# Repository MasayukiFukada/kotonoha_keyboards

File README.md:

# ことのは キーボード(Kotonoha Keyboards)

My designed mechanical keyboards.

Firmware is [here](https://github.com/MasayukiFukada/qmk_firmware/tree/append_minamo_keymaps/keyboards/kotonoha) (QMK fork)  
※ `append_minamo_keymaps` branch

## ことのは 『盆栽』(Kotonoha - type "BONSAI")

* 30 % Keyboard (30 Key)
* FreeStyle Staggered
* PCB and Acrylic plate

## ことのは 『居合』(Kotonoha - type "IAI")

* 30 % Keyboard (30 Key)
* 6 x 2 OrtholinearBar
* PCB and Acrylic plate

## ことのは 『侘寂』(Kotonoha - type "WABISABI")

* 30 % Keyboard (30 Key)
* Matrix Staggered (Row x Column Staggered)
* PCB and Acrylic plate

## License

MIT

KiCad のフットプリントは [@foostan](https://github.com/foostan) さんのライブラリ  
[kbd](https://github.com/foostan/kbd) から使用させて頂きました。  
foostan さんありがとうございました。

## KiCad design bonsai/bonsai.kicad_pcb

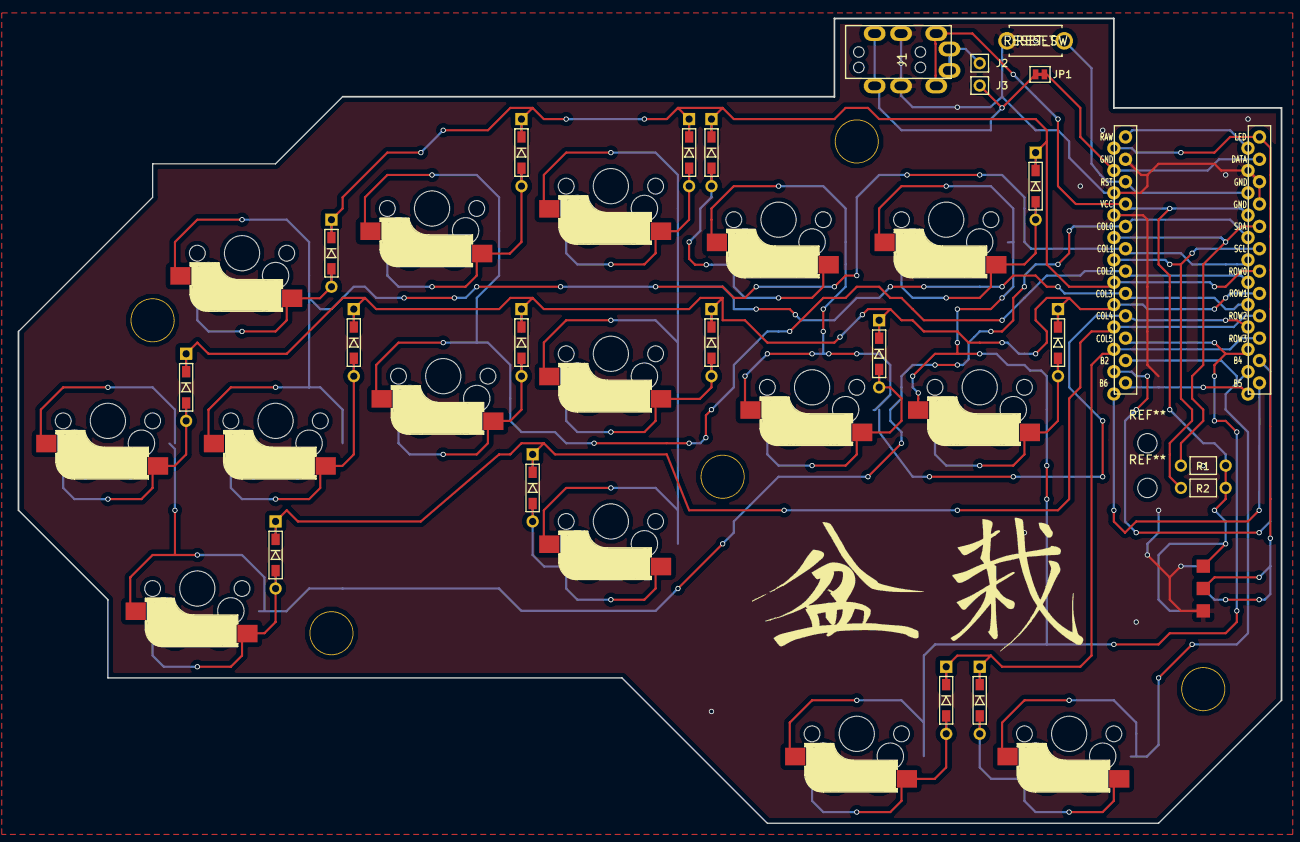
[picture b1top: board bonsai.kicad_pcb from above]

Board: 2 copper layers, 143.5 x 91.4 mm, 44 parts (0 on the bottom side), 35 nets.

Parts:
D1, D2, D3, D4, D5, D6, D7, D8, D9, D10, D11, D12, D13, D14, D15: D; D3_TH_SMD
J1: MJ-4PP-9
J2, J3: i2c_pin; 1pin_conn
J4: LED; StripLED_rev
JP1: Jumper; JP
R1, R2: R
Ref**: Val**; HOLE
Ref**#2, Ref**#3, Ref**#4, Ref**#5: Val**; HOLE
SW1: RESET_SW; ResetSW
SW2, SW3, SW4, SW5, SW6, SW7, SW8, SW9, SW10, SW11, SW12, SW13, SW14, SW15, SW16: SW_PUSH; CherryMX_Hotswap
U1: ProMicro; ProMicro_v2

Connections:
COL0: SW2.1, SW3.1, U1.20
COL1: SW4.1, SW5.1, U1.19
COL2: SW6.1, SW7.1, U1.18
COL3: SW8.1, SW9.1, SW10.1, U1.17
COL4: SW11.1, SW12.1, U1.16
COL5: SW13.1, SW14.1, SW15.1, U1.15
COL6: SW16.1, U1.14
DATA: JP1.1, U1.2
GND: J1.C, J4.1, SW1.2, U1.3, U1.4, U1.23
LED: J4.2, U1.1
unnamed: D1.2, SW2.2
unnamed: D2.2, SW3.2
unnamed: D3.2, SW4.2
unnamed: D4.2, SW5.2
unnamed: D5.2, SW6.2
unnamed: D6.2, SW7.2
unnamed: D7.2, SW8.2
unnamed: D8.2, SW9.2
unnamed: D9.2, SW10.2
unnamed: D10.2, SW11.2
unnamed: D11.2, SW12.2
unnamed: D12.2, SW13.2
unnamed: D13.2, SW14.2
unnamed: D14.2, SW15.2
unnamed: D15.2, SW16.2
unnamed: J1.A, J2.1
unnamed: J1.B, J3.1, JP1.2
unnamed: SW1.1, U1.22
ROW0: D3.1, D5.1, D7.1, D10.1, D12.1, U1.7
ROW1: D1.1, D4.1, D6.1, D8.1, D11.1, D13.1, U1.8
ROW2: D2.1, D9.1, U1.9
ROW3: D14.1, D15.1, U1.10
SCL: R2.2, U1.6
SDA: R1.2, U1.5
VCC: J1.D, J4.3, R1.1, R2.1, U1.21

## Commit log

2019-05-05 :seedling: 基板データとアクリルプレートデータを公開
2019-05-05 :wrench: Tweak
2019-05-17 :earth_asia: refine
